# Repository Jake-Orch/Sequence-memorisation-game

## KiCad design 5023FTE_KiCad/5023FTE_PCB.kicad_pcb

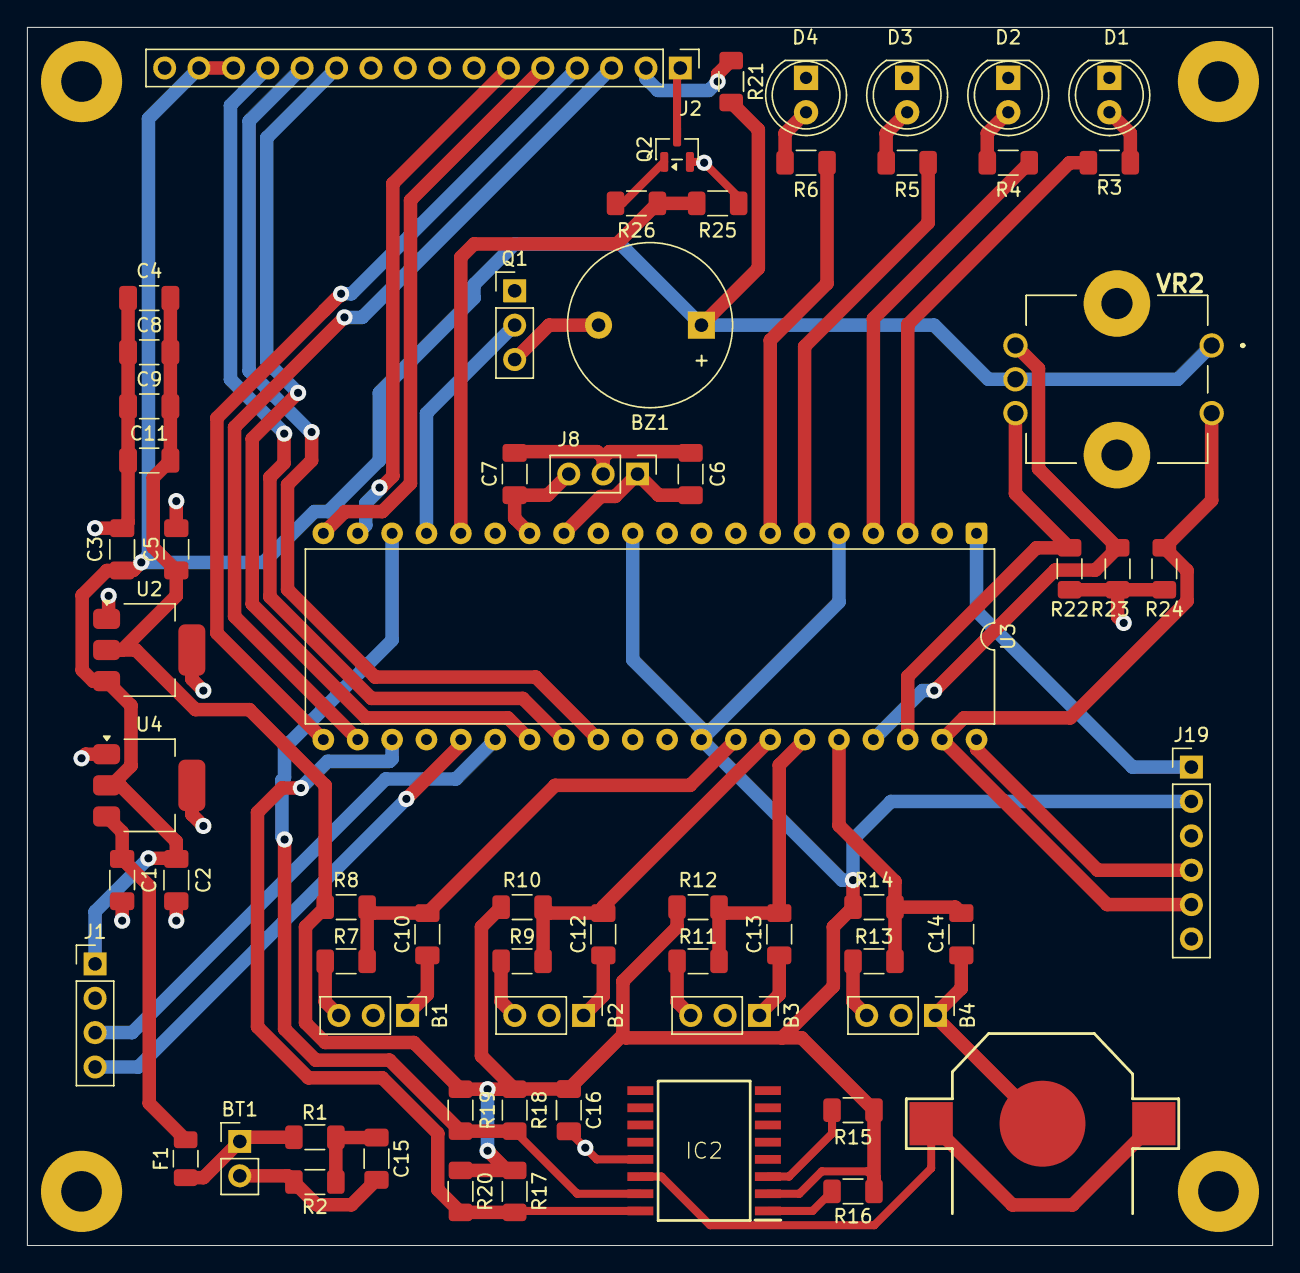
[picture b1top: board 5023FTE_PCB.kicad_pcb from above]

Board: 2 copper layers, 92.0 x 90.0 mm, 65 parts (0 on the bottom side), 49 nets.

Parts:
B1, B2, B3, B4: Conn_01x03_Socket; PinHeader_1x03_P2.54mm_Vertical
BT1: Battery; PinHeader_1x02_P2.54mm_Vertical
BT2: Coin Battery Cell; CR1220
BZ1: Buzzer; Buzzer_12x9.5RM7.6
C1: 0.33uF; C_1206_3216Metric_Pad1.33x1.80mm_HandSolder
C2, C4, C8, C9, C11, C15, C16: 0.1uF; C_1206_3216Metric_Pad1.33x1.80mm_HandSolder
C3, C5: 10uF; C_1206_3216Metric_Pad1.33x1.80mm_HandSolder
C6, C7: 18pF; C_1206_3216Metric_Pad1.33x1.80mm_HandSolder
C10, C12, C13: 1nF; C_1206_3216Metric_Pad1.33x1.80mm_HandSolder
C14: C; C_1206_3216Metric_Pad1.33x1.80mm_HandSolder
D1, D2, D3, D4: LED; LED_D5.0mm
F1: 1A; Fuse_1206_3216Metric
IC2: SOIC127P1032X265-16N
J1: BT Header; PinHeader_1x04_P2.54mm_Vertical
J2: Conn_01x16_Pin; PinHeader_1x16_P2.54mm_Vertical
J8: MA03-1; PinHeader_1x03_P2.54mm_Vertical
J19: MA06-1; PinHeader_1x06_P2.54mm_Vertical
Q1: 2N3904; PinHeader_1x03_P2.54mm_Vertical
Q2: BSS138; SOT-23
R1, R2, R3, R4, R5, R6: R; R_1206_3216Metric_Pad1.30x1.75mm_HandSolder
R7, R9, R11, R13, R26: 1k; R_1206_3216Metric_Pad1.30x1.75mm_HandSolder
R8, R10, R12, R14, R15, R16, R17, R18, R25: 10k; R_1206_3216Metric_Pad1.30x1.75mm_HandSolder
R19, R20: 2k2; R_1206_3216Metric_Pad1.30x1.75mm_HandSolder
R21: 100; R_1206_3216Metric_Pad1.30x1.75mm_HandSolder
R22, R23, R24: 5k6; R_1206_3216Metric_Pad1.30x1.75mm_HandSolder
U2: LM1117T-3.3; SOT-223
U3: PIC18F4520-xP; DIP-40_W15.24mm
U4: LM1117DT-5.0; SOT-223
VR2: PEC12R4230FS0024

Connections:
3V3: C4.1, C5.1, C8.1, C9.1, C11.1, C16.1, IC2.2 (VCC), J19.2, R8.2, R10.2, R12.2, R14.2, R15.2, R16.1, R17.1, R18.1, R19.1, R20.1, U2.2 (VO), U3.5 (RA3), U3.11 (VDD), U3.32 (VDD)
5V: BZ1.1 (+), C2.1, C3.1, J1.1, J2.14, J2.15, R21.2, U2.3 (VI), U4.2 (VO), VR2.C1 (CW), VR2.D1 (NO_1)
/32KHZ: IC2.1 (32KHZ), R16.2
/SQW/INT: IC2.3 (~INT/SQW), R15.1
GND: B1.1, B2.1, B3.1, B4.1, BT1.2 (-), BT2.GND, C1.2, C2.2, C3.2, C4.2, C5.2, C6.2, C7.2, C8.2, C9.2, C10.1, C11.2, C12.1, C13.1, C14.1, C15.2, C16.2, D1.1 (K), D2.1 (K), D3.1 (K), D4.1 (K), IC2.13 (GND), J1.2, J2.16, J8.2, J19.3, Q1.1 (E), Q2.2 (S), R2.2, R22.2, R23.1, R24.2, R25.2, U2.1 (GND), U2.4, U3.12 (VSS), U3.31 (VSS), U4.1 (GND), U4.4
MCLR: J19.1, U3.1 (RE3/~MCLR)
unnamed: B1.3, R7.1
unnamed: B2.3, R9.1
unnamed: B3.3, R11.1
unnamed: B4.3, R13.1
unnamed: BT1.1 (+), F1.1, R1.1
unnamed: BZ1.2 (-), Q1.3 (C)
unnamed: C15.1, R1.2, R2.1
unnamed: D1.2 (A), R3.1
unnamed: D2.2 (A), R4.1
unnamed: D3.2 (A), R5.1
unnamed: D4.2 (A), R6.1
unnamed: J2.1, Q2.3 (D)
unnamed: J2.2, R21.1
unnamed: Q2.1 (G), R26.1
unnamed: C1.1, F1.2, U4.3 (VI)
OSC1: C6.1, J8.1, U3.13 (RA7)
OSC2: C7.1, J8.3, U3.14 (RA6)
PGC: J19.5, R24.1, U3.39 (RB6), VR2.E1 (NO_2)
PGD: J19.4, U3.40 (RB7)
RA1: R3.2, U3.3 (RA1)
RA2: R4.2, U3.4 (RA2)
RA4: R5.2, U3.6 (RA4)
RA5: R6.2, U3.7 (RA5)
RB0: C10.2, R7.2, R8.1, U3.33 (RB0)
RB1: C12.2, R9.2, R10.1, U3.34 (RB1)
RB2: C13.2, R11.2, R12.1, U3.35 (RB2)
RB3: C14.2, R13.2, R14.1, U3.36 (RB3)
RB4: R23.2, U3.37 (RB4), VR2.A1 (CCW)
RB5: R22.1, U3.38 (RB5), VR2.B1 (WIPER)
RC1: R25.1, R26.2, U3.16 (RC1)
RC2: Q1.2 (B), U3.17 (RC2)
RC3: IC2.15 (SDA), R18.2, R19.2, U3.18 (RC3)
RC4: IC2.16 (SCL), R17.2, R20.2, U3.23 (RC4)
RC6: J1.4, U3.25 (RC6)
RC7: J1.3, U3.26 (RC7)
RD0/RB8_32: J2.6, U3.19 (RD0)
RD1/RB9_32: J2.5, U3.20 (RD1)
RD2/RB10_32: J2.4, U3.21 (RD2)
RD3/RB11_32: J2.3, U3.22 (RD3)
RD4/RB12_32: J2.11, U3.27 (RD4)
RD5/RB13_32: J2.13, U3.28 (RD5)
RD6/RB14_32: J2.12, U3.29 (RD6)
VBAT: BT2.VBAT, IC2.14 (VBAT)

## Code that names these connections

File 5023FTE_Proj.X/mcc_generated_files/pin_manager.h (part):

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#define RA3_SetHigh()            do { LATAbits.LATA3 = 1; } while(0)
#define RA3_SetLow()             do { LATAbits.LATA3 = 0; } while(0)
#define RA3_Toggle()             do { LATAbits.LATA3 = ~LATAbits.LATA3; } while(0)
#define RA3_GetValue()              PORTAbits.RA3
#define RA3_SetDigitalInput()    do { TRISAbits.TRISA3 = 1; } while(0)
#define RA3_SetDigitalOutput()   do { TRISAbits.TRISA3 = 0; } while(0)
#define RA3_SetAnalogMode()         do { ANSELbits.ANS3 = 1; } while(0)
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#define RB0_SetHigh()            do { LATBbits.LATB0 = 1; } while(0)
#define RB0_SetLow()             do { LATBbits.LATB0 = 0; } while(0)
#define RB0_Toggle()             do { LATBbits.LATB0 = ~LATBbits.LATB0; } while(0)
#define RB0_GetValue()              PORTBbits.RB0
#define RB0_SetDigitalInput()    do { TRISBbits.TRISB0 = 1; } while(0)
#define RB0_SetDigitalOutput()   do { TRISBbits.TRISB0 = 0; } while(0)
#define RB0_SetPullup()             do { WPUBbits.WPUB0 = 1; } while(0)
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#define RB1_SetHigh()            do { LATBbits.LATB1 = 1; } while(0)
#define RB1_SetLow()             do { LATBbits.LATB1 = 0; } while(0)
#define RB1_Toggle()             do { LATBbits.LATB1 = ~LATBbits.LATB1; } while(0)
#define RB1_GetValue()              PORTBbits.RB1
#define RB1_SetDigitalInput()    do { TRISBbits.TRISB1 = 1; } while(0)
#define RB1_SetDigitalOutput()   do { TRISBbits.TRISB1 = 0; } while(0)
#define RB1_SetPullup()             do { WPUBbits.WPUB1 = 1; } while(0)
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#define RB2_SetHigh()            do { LATBbits.LATB2 = 1; } while(0)
#define RB2_SetLow()             do { LATBbits.LATB2 = 0; } while(0)
#define RB2_Toggle()             do { LATBbits.LATB2 = ~LATBbits.LATB2; } while(0)
#define RB2_GetValue()              PORTBbits.RB2
#define RB2_SetDigitalInput()    do { TRISBbits.TRISB2 = 1; } while(0)
#define RB2_SetDigitalOutput()   do { TRISBbits.TRISB2 = 0; } while(0)
#define RB2_SetPullup()             do { WPUBbits.WPUB2 = 1; } while(0)
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#define RC1_SetHigh()            do { LATCbits.LATC1 = 1; } while(0)
#define RC1_SetLow()             do { LATCbits.LATC1 = 0; } while(0)
#define RC1_Toggle()             do { LATCbits.LATC1 = ~LATCbits.LATC1; } while(0)
#define RC1_GetValue()              PORTCbits.RC1
#define RC1_SetDigitalInput()    do { TRISCbits.TRISC1 = 1; } while(0)
#define RC1_SetDigitalOutput()   do { TRISCbits.TRISC1 = 0; } while(0)

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#define RC3_SetHigh()            do { LATCbits.LATC3 = 1; } while(0)
#define RC3_SetLow()             do { LATCbits.LATC3 = 0; } while(0)
#define RC3_Toggle()             do { LATCbits.LATC3 = ~LATCbits.LATC3; } while(0)
#define RC3_GetValue()              PORTCbits.RC3
#define RC3_SetDigitalInput()    do { TRISCbits.TRISC3 = 1; } while(0)
#define RC3_SetDigitalOutput()   do { TRISCbits.TRISC3 = 0; } while(0)

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#define RC4_SetHigh()            do { LATCbits.LATC4 = 1; } while(0)
#define RC4_SetLow()             do { LATCbits.LATC4 = 0; } while(0)
#define RC4_Toggle()             do { LATCbits.LATC4 = ~LATCbits.LATC4; } while(0)
#define RC4_GetValue()              PORTCbits.RC4
#define RC4_SetDigitalInput()    do { TRISCbits.TRISC4 = 1; } while(0)
#define RC4_SetDigitalOutput()   do { TRISCbits.TRISC4 = 0; } while(0)

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#define RC6_SetHigh()            do { LATCbits.LATC6 = 1; } while(0)
#define RC6_SetLow()             do { LATCbits.LATC6 = 0; } while(0)
#define RC6_Toggle()             do { LATCbits.LATC6 = ~LATCbits.LATC6; } while(0)
#define RC6_GetValue()              PORTCbits.RC6
#define RC6_SetDigitalInput()    do { TRISCbits.TRISC6 = 1; } while(0)
#define RC6_SetDigitalOutput()   do { TRISCbits.TRISC6 = 0; } while(0)

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#define RC7_SetHigh()            do { LATCbits.LATC7 = 1; } while(0)
#define RC7_SetLow()             do { LATCbits.LATC7 = 0; } while(0)
#define RC7_Toggle()             do { LATCbits.LATC7 = ~LATCbits.LATC7; } while(0)
#define RC7_GetValue()              PORTCbits.RC7
#define RC7_SetDigitalInput()    do { TRISCbits.TRISC7 = 1; } while(0)
#define RC7_SetDigitalOutput()   do { TRISCbits.TRISC7 = 0; } while(0)

// get/set IO_RD0 aliases
#define IO_RD0_TRIS                 TRISDbits.TRISD0
#define IO_RD0_LAT                  LATDbits.LATD0
#define IO_RD0_PORT                 PORTDbits.RD0
#define IO_RD0_SetHigh()            do { LATDbits.LATD0 = 1; } while(0)
#define IO_RD0_SetLow()             do { LATDbits.LATD0 = 0; } while(0)
#define IO_RD0_Toggle()             do { LATDbits.LATD0 = ~LATDbits.LATD0; } while(0)
#define IO_RD0_GetValue()           PORTDbits.RD0
#define IO_RD0_SetDigitalInput()    do { TRISDbits.TRISD0 = 1; } while(0)
#define IO_RD0_SetDigitalOutput()   do { TRISDbits.TRISD0 = 0; } while(0)

// get/set IO_RD1 aliases
#define IO_RD1_TRIS                 TRISDbits.TRISD1
#define IO_RD1_LAT                  LATDbits.LATD1
#define IO_RD1_PORT                 PORTDbits.RD1
#define IO_RD1_SetHigh()            do { LATDbits.LATD1 = 1; } while(0)
#define IO_RD1_SetLow()             do { LATDbits.LATD1 = 0; } while(0)
#define IO_RD1_Toggle()             do { LATDbits.LATD1 = ~LATDbits.LATD1; } while(0)
#define IO_RD1_GetValue()           PORTDbits.RD1
#define IO_RD1_SetDigitalInput()    do { TRISDbits.TRISD1 = 1; } while(0)
#define IO_RD1_SetDigitalOutput()   do { TRISDbits.TRISD1 = 0; } while(0)

// get/set IO_RD2 aliases
#define IO_RD2_TRIS                 TRISDbits.TRISD2
#define IO_RD2_LAT                  LATDbits.LATD2
#define IO_RD2_PORT                 PORTDbits.RD2
#define IO_RD2_SetHigh()            do { LATDbits.LATD2 = 1; } while(0)
#define IO_RD2_SetLow()             do { LATDbits.LATD2 = 0; } while(0)
#define IO_RD2_Toggle()             do { LATDbits.LATD2 = ~LATDbits.LATD2; } while(0)
#define IO_RD2_GetValue()           PORTDbits.RD2
#define IO_RD2_SetDigitalInput()    do { TRISDbits.TRISD2 = 1; } while(0)
#define IO_RD2_SetDigitalOutput()   do { TRISDbits.TRISD2 = 0; } while(0)

// get/set IO_RD3 aliases
#define IO_RD3_TRIS                 TRISDbits.TRISD3
#define IO_RD3_LAT                  LATDbits.LATD3
#define IO_RD3_PORT                 PORTDbits.RD3
#define IO_RD3_SetHigh()            do { LATDbits.LATD3 = 1; } while(0)
#define IO_RD3_SetLow()             do { LATDbits.LATD3 = 0; } while(0)
#define IO_RD3_Toggle()             do { LATDbits.LATD3 = ~LATDbits.LATD3; } while(0)
#define IO_RD3_GetValue()           PORTDbits.RD3
#define IO_RD3_SetDigitalInput()    do { TRISDbits.TRISD3 = 1; } while(0)
#define IO_RD3_SetDigitalOutput()   do { TRISDbits.TRISD3 = 0; } while(0)

// get/set IO_RD4 aliases
#define IO_RD4_TRIS                 TRISDbits.TRISD4
#define IO_RD4_LAT                  LATDbits.LATD4
#define IO_RD4_PORT                 PORTDbits.RD4
#define IO_RD4_SetHigh()            do { LATDbits.LATD4 = 1; } while(0)
#define IO_RD4_SetLow()             do { LATDbits.LATD4 = 0; } while(0)
#define IO_RD4_Toggle()             do { LATDbits.LATD4 = ~LATDbits.LATD4; } while(0)
#define IO_RD4_GetValue()           PORTDbits.RD4
#define IO_RD4_SetDigitalInput()    do { TRISDbits.TRISD4 = 1; } while(0)
#define IO_RD4_SetDigitalOutput()   do { TRISDbits.TRISD4 = 0; } while(0)

// get/set IO_RD5 aliases
#define IO_RD5_TRIS                 TRISDbits.TRISD5
#define IO_RD5_LAT                  LATDbits.LATD5
#define IO_RD5_PORT                 PORTDbits.RD5
#define IO_RD5_SetHigh()            do { LATDbits.LATD5 = 1; } while(0)
#define IO_RD5_SetLow()             do { LATDbits.LATD5 = 0; } while(0)
#define IO_RD5_Toggle()             do { LATDbits.LATD5 = ~LATDbits.LATD5; } while(0)
#define IO_RD5_GetValue()           PORTDbits.RD5
#define IO_RD5_SetDigitalInput()    do { TRISDbits.TRISD5 = 1; } while(0)
#define IO_RD5_SetDigitalOutput()   do { TRISDbits.TRISD5 = 0; } while(0)

// get/set IO_RD6 aliases
#define IO_RD6_TRIS                 TRISDbits.TRISD6
#define IO_RD6_LAT                  LATDbits.LATD6
#define IO_RD6_PORT                 PORTDbits.RD6
#define IO_RD6_SetHigh()            do { LATDbits.LATD6 = 1; } while(0)
#define IO_RD6_SetLow()             do { LATDbits.LATD6 = 0; } while(0)
#define IO_RD6_Toggle()             do { LATDbits.LATD6 = ~LATDbits.LATD6; } while(0)
#define IO_RD6_GetValue()           PORTDbits.RD6
#define IO_RD6_SetDigitalInput()    do { TRISDbits.TRISD6 = 1; } while(0)
#define IO_RD6_SetDigitalOutput()   do { TRISDbits.TRISD6 = 0; } while(0)

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
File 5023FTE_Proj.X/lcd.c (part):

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#endif                                      //                                      */
#ifdef xc8                                  // If XC8 is used - no support for F4520*/
    ANSELbits.ANS0   = 0;                   // Disable analogue functions on RA0    */
    ANSELbits.ANS1   = 0;                   // Disable analogue functions on RA1    */
    ANSELbits.ANS2   = 0;                   // Disable analogue functions on RA2    */
    ANSELbits.ANS3   = 0;                   // Disable analogue functions on RA3    */
    ANSELbits.ANS4   = 0;                   // Disable analogue functions on RA5    */
    SLRCONbits.SLRA  = 0;                   // Set PORTA slew rate to standard      */
#endif                                      //                                      */
#   define  DATA_PORT        LATA           // DATA_PORT macro is LATA              */
#   define  TRIS_DATA_PORT   TRISA          // TRIS_DATA_PORT macro is TRISA        */
#   define  RS_PIN           LATAbits.LATA5 // Register Select pin is RA5 on PORTA  */
#   define  E_PIN            LATAbits.LATA4 // Enable pin is RA4 on PORTA           */
#endif                                      //                                      */
                                            //                                      */
#ifdef DATA_PORTB                           // If LCD is used on PORTB              */
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    INTCON2bits.RBPU = 1;                   // Internal port B Pull-Ups off         */
#   define  DATA_PORT        LATB           // DATA_PORT macro is LATB              */
#   define  TRIS_DATA_PORT   TRISB          // TRIS_DATA_PORT macro is TRISA        */
#   define  RW_PIN           LATBbits.LATB6 // Read/Write pin is RB6 on PORTB       */
#   define  RS_PIN           LATBbits.LATB5 // Register Select pin is RB5 on PORTB  */
#   define  E_PIN            LATBbits.LATB4 // Enable pin is RB4 on PORTB           */
#endif                                      //                                      */
#ifdef DATA_PORTC                           // If LCD is used on PORTC              */
#   define  DATA_PORT        LATC           // DATA_PORT macro is LATC              */
#   define  TRIS_DATA_PORT   TRISC          // TRIS_DATA_PORT macro is TRISC        */
#   define  RW_PIN           LATCbits.LATC6 // Read/Write pin is RB6 on PORTB       */
#   define  RS_PIN           LATCbits.LATC5 // Register Select pin is RB5 on PORTB  */
#   define  E_PIN            LATCbits.LATC4 // Enable pin is RB4 on PORTB           */
#endif                                      //                                      */
                                            //                                      */
#ifdef DATA_PORTD                           // If LCD is used on PORTD              */
#   define  DATA_PORT        LATD           // DATA_PORT macro is LATD              */
#   define  TRIS_DATA_PORT   TRISD          // TRIS_DATA_PORT macro is TRISD        */
#   define  RW_PIN           LATDbits.LATD6 // Read/Write pin is RB6 on PORTB       */
#   define  RS_PIN           LATDbits.LATD5 // Register Select pin is RB5 on PORTB  */
#   define  E_PIN            LATDbits.LATD4 // Enable pin is RB4 on PORTB           */
#endif                                      //                                      */
    DATA_PORT      = 0;                     // Latch DATA_PORT to 0                 */
    TRIS_DATA_PORT = 0;                     // Make DATA_PORT all output            */
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
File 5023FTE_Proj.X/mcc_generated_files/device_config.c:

/**
  @Generated PIC10 / PIC12 / PIC16 / PIC18 MCUs Source File

  @Company:
    Microchip Technology Inc.

  @File Name:
    mcc.c

  @Summary:
    This is the device_config.c file generated using PIC10 / PIC12 / PIC16 / PIC18 MCUs

  @Description:
    This header file provides implementations for driver APIs for all modules selected in the GUI.
    Generation Information :
        Product Revision  :  PIC10 / PIC12 / PIC16 / PIC18 MCUs - 1.81.8
        Device            :  PIC18F45K20
        Driver Version    :  2.00
    The generated drivers are tested against the following:
        Compiler          :  XC8 2.36 and above or later
        MPLAB             :  MPLAB X 6.00
*/

/*
    (c) 2018 Microchip Technology Inc. and its subsidiaries. 
    
    Subject to your compliance with these terms, you may use Microchip software and any 
    derivatives exclusively with Microchip products. It is your responsibility to comply with third party 
    license terms applicable to your use of third party software (including open source software) that 
    may accompany Microchip software.
    
    THIS SOFTWARE IS SUPPLIED BY MICROCHIP "AS IS". NO WARRANTIES, WHETHER 
    EXPRESS, IMPLIED OR STATUTORY, APPLY TO THIS SOFTWARE, INCLUDING ANY 
    IMPLIED WARRANTIES OF NON-INFRINGEMENT, MERCHANTABILITY, AND FITNESS 
    FOR A PARTICULAR PURPOSE.
    
    IN NO EVENT WILL MICROCHIP BE LIABLE FOR ANY INDIRECT, SPECIAL, PUNITIVE, 
    INCIDENTAL OR CONSEQUENTIAL LOSS, DAMAGE, COST OR EXPENSE OF ANY KIND 
    WHATSOEVER RELATED TO THE SOFTWARE, HOWEVER CAUSED, EVEN IF MICROCHIP 
    HAS BEEN ADVISED OF THE POSSIBILITY OR THE DAMAGES ARE FORESEEABLE. TO 
    THE FULLEST EXTENT ALLOWED BY LAW, MICROCHIP'S TOTAL LIABILITY ON ALL 
    CLAIMS IN ANY WAY RELATED TO THIS SOFTWARE WILL NOT EXCEED THE AMOUNT 
    OF FEES, IF ANY, THAT YOU HAVE PAID DIRECTLY TO MICROCHIP FOR THIS 
    SOFTWARE.
*/

// Configuration bits: selected in the GUI

// CONFIG1H
#pragma config FOSC = HS    // Oscillator Selection bits->HS oscillator
#pragma config FCMEN = OFF    // Fail-Safe Clock Monitor Enable bit->Fail-Safe Clock Monitor disabled
#pragma config IESO = OFF    // Internal/External Oscillator Switchover bit->Oscillator Switchover mode disabled

// CONFIG2L
#pragma config PWRT = OFF    // Power-up Timer Enable bit->PWRT disabled
#pragma config BOREN = SBORDIS    // Brown-out Reset Enable bits->Brown-out Reset enabled in hardware only (SBOREN is disabled)
#pragma config BORV = 18    // Brown Out Reset Voltage bits->VBOR set to 1.8 V nominal

// CONFIG2H
#pragma config WDTEN = OFF    // Watchdog Timer Enable bit->WDT is controlled by SWDTEN bit of the WDTCON register
#pragma config WDTPS = 32768    // Watchdog Timer Postscale Select bits->1:32768

// CONFIG3H
#pragma config CCP2MX = PORTC    // CCP2 MUX bit->CCP2 input/output is multiplexed with RC1
#pragma config PBADEN = OFF    // PORTB A/D Enable bit->PORTB<4:0> pins are configured as analog input channels on Reset
#pragma config LPT1OSC = OFF    // Low-Power Timer1 Oscillator Enable bit->Timer1 configured for higher power operation
#pragma config HFOFST = ON    // HFINTOSC Fast Start-up->HFINTOSC starts clocking the CPU without waiting for the oscillator to stablize.
#pragma config MCLRE = ON    // MCLR Pin Enable bit->MCLR pin enabled; RE3 input pin disabled

// CONFIG4L
#pragma config STVREN = ON    // Stack Full/Underflow Reset Enable bit->Stack full/underflow will cause Reset
#pragma config LVP = OFF    // Single-Supply ICSP Enable bit->Single-Supply ICSP disabled
#pragma config XINST = OFF    // Extended Instruction Set Enable bit->Instruction set extension and Indexed Addressing mode disabled (Legacy mode)
#pragma config DEBUG = OFF    // Background Debugger Enable bit->Background debugger disabled, RB6 and RB7 configured as general purpose I/O pins

// CONFIG5L
#pragma config CP0 = OFF    // Code Protection Block 0->Block 0 (000800-001FFFh) not code-protected
#pragma config CP1 = OFF    // Code Protection Block 1->Block 1 (002000-003FFFh) not code-protected
#pragma config CP2 = OFF    // Code Protection Block 2->Block 2 (004000-005FFFh) not code-protected
#pragma config CP3 = OFF    // Code Protection Block 3->Block 3 (006000-007FFFh) not code-protected

// CONFIG5H
#pragma config CPB = OFF    // Boot Block Code Protection bit->Boot block (000000-0007FFh) not code-protected
#pragma config CPD = OFF    // Data EEPROM Code Protection bit->Data EEPROM not code-protected

// CONFIG6L
#pragma config WRT0 = OFF    // Write Protection Block 0->Block 0 (000800-001FFFh) not write-protected
#pragma config WRT1 = OFF    // Write Protection Block 1->Block 1 (002000-003FFFh) not write-protected
#pragma config WRT2 = OFF    // Write Protection Block 2->Block 2 (004000-005FFFh) not write-protected
#pragma config WRT3 = OFF    // Write Protection Block 3->Block 3 (006000-007FFFh) not write-protected

// CONFIG6H
#pragma config WRTC = OFF    // Configuration Register Write Protection bit->Configuration registers (300000-3000FFh) not write-protected
#pragma config WRTB = OFF    // Boot Block Write Protection bit->Boot Block (000000-0007FFh) not write-protected
#pragma config WRTD = OFF    // Data EEPROM Write Protection bit->Data EEPROM not write-protected

// CONFIG7L
#pragma config EBTR0 = OFF    // Table Read Protection Block 0->Block 0 (000800-001FFFh) not protected from table reads executed in other blocks
#pragma config EBTR1 = OFF    // Table Read Protection Block 1->Block 1 (002000-003FFFh) not protected from table reads executed in other blocks
#pragma config EBTR2 = OFF    // Table Read Protection Block 2->Block 2 (004000-005FFFh) not protected from table reads executed in other blocks
#pragma config EBTR3 = OFF    // Table Read Protection Block 3->Block 3 (006000-007FFFh) not protected from table reads executed in other blocks

// CONFIG7H
#pragma config EBTRB = OFF    // Boot Block Table Read Protection bit->Boot Block (000000-0007FFh) not protected from table reads executed in other blocks
